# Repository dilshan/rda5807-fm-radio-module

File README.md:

# FM stereo receiver module

This is an RDA5807 based FM stereo radio module. This module is designed to replace old, low-voltage, analog FM stereo receiver modules. Like many digital receivers, this module also got auto scanning, station memory, and digital volume control. This module can driver using 5V to 9V DC power source.

The frequency range of the receiver is 88MHz to 108MHz. The auto scanner of this module can tune the receiver with 25kHz increments in up and down directions. 

The memory manager available with the current firmware can hold up to 10 stations in MCU EEPROM. 

AF output power of this module is not sufficient to handle the pair of speakers. To drive speakers, this module needs to pair with a stereo AF power amplifier kit/module.

This is a [certified open-source hardware project](https://certification.oshwa.org/lk000014.html). All the design files, [documentation](https://github.com/dilshan/rda5807-fm-radio-module/wiki), and firmware source code are available to download at the [project source repository](https://github.com/dilshan/rda5807-fm-radio-module/tree/main/firmware). Content of this project is distributed under the terms of the following license:

 - Hardware License: [CERN-OHL-W](https://opensource.org/CERN-OHL-W)
 - Software License: [MIT License](https://github.com/dilshan/rda5807-fm-radio-module/blob/main/LICENSE)
 - Documentation License: [CC BY 4.0](https://creativecommons.org/licenses/by/4.0)

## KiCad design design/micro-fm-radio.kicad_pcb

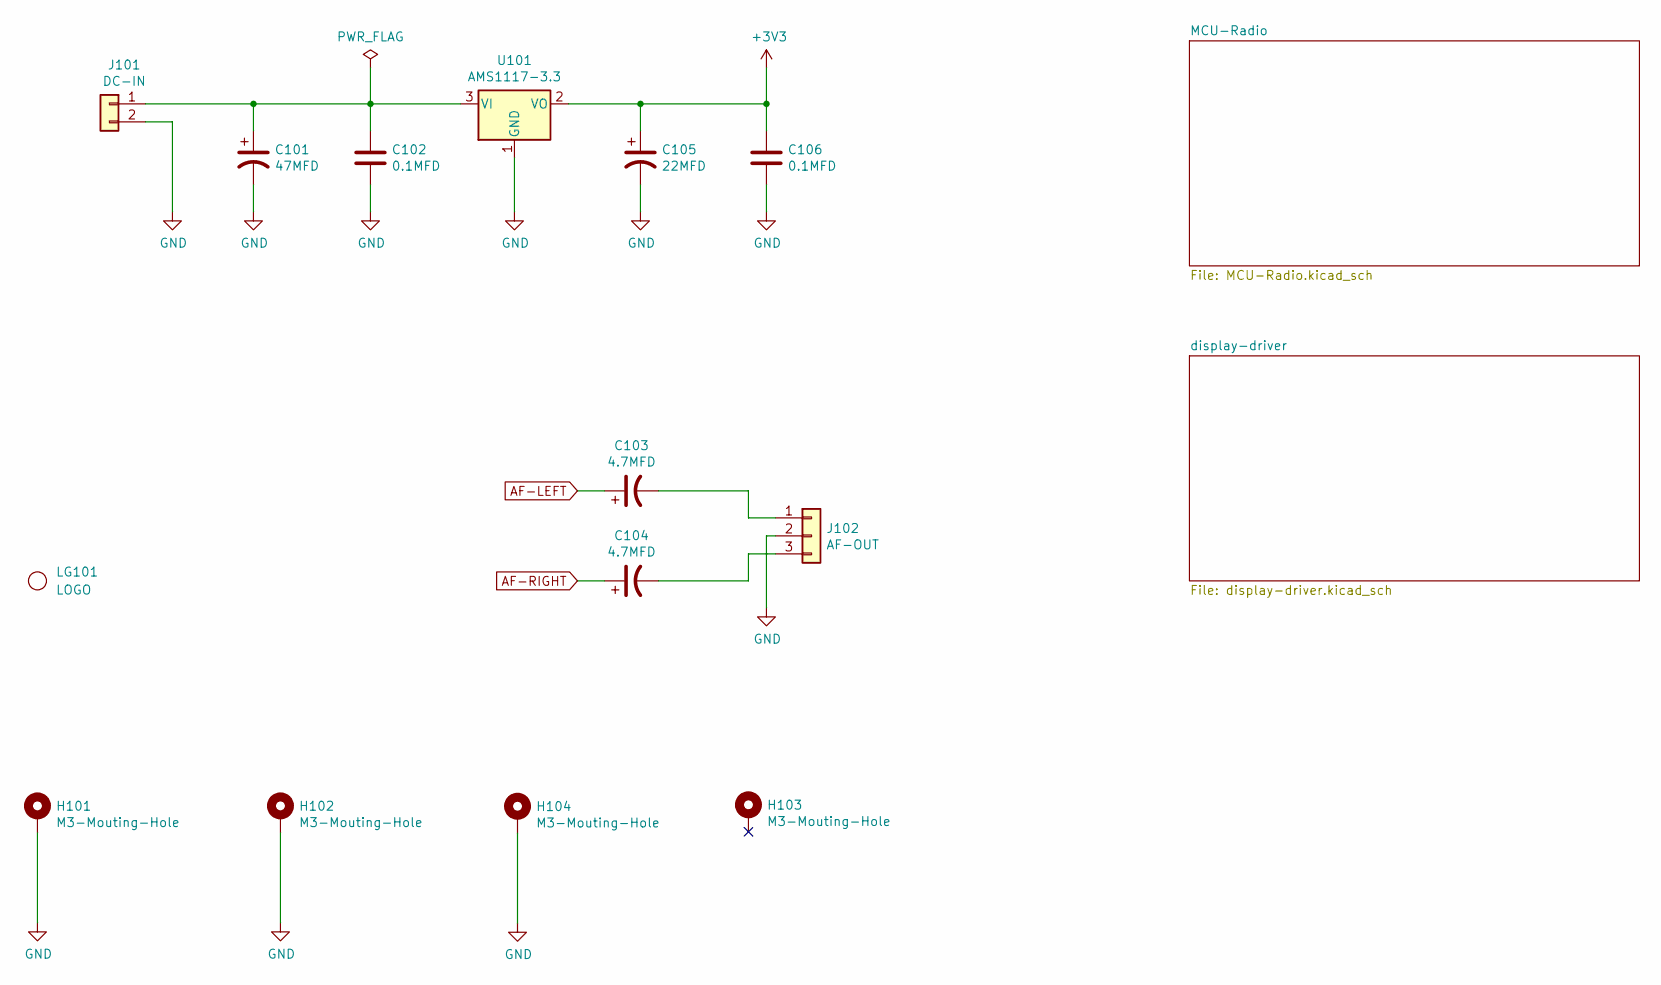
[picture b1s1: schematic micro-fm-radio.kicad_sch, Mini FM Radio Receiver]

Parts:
C101: 47MFD; CP_Radial_D5.0mm_P2.50mm
C102, C106: 0.1MFD; C_0805_2012Metric_Pad1.18x1.45mm_HandSolder
C103, C104: 4.7MFD; CP_Radial_D5.0mm_P2.50mm
C105: 22MFD; CP_Radial_D5.0mm_P2.50mm
H101, H102, H103, H104: M3-Mouting-Hole; MountingHole_3.2mm_M3_Pad
J101: DC-IN; PhoenixContact_MCV_1,5_2-G-3.5_1x02_P3.50mm_Vertical
J102: AF-OUT; PinHeader_1x03_P2.54mm_Vertical
LG101: LOGO; elect-6mm
U101: AMS1117-3.3; SOT-223-3_TabPin2

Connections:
+3V3: C105.1, C106.1, U101.2 (VO); also elsewhere on the board
AF-LEFT: C103.1; also elsewhere on the board
AF-RIGHT: C104.1; also elsewhere on the board
GND: C101.2, C102.2, C105.2, C106.2, H101.1, H102.1, H104.1, J101.2, J102.2, U101.1 (GND); also elsewhere on the board
unnamed: C101.1, C102.1, J101.1, U101.3 (VI)
unnamed: C103.2, J102.1
unnamed: C104.2, J102.3

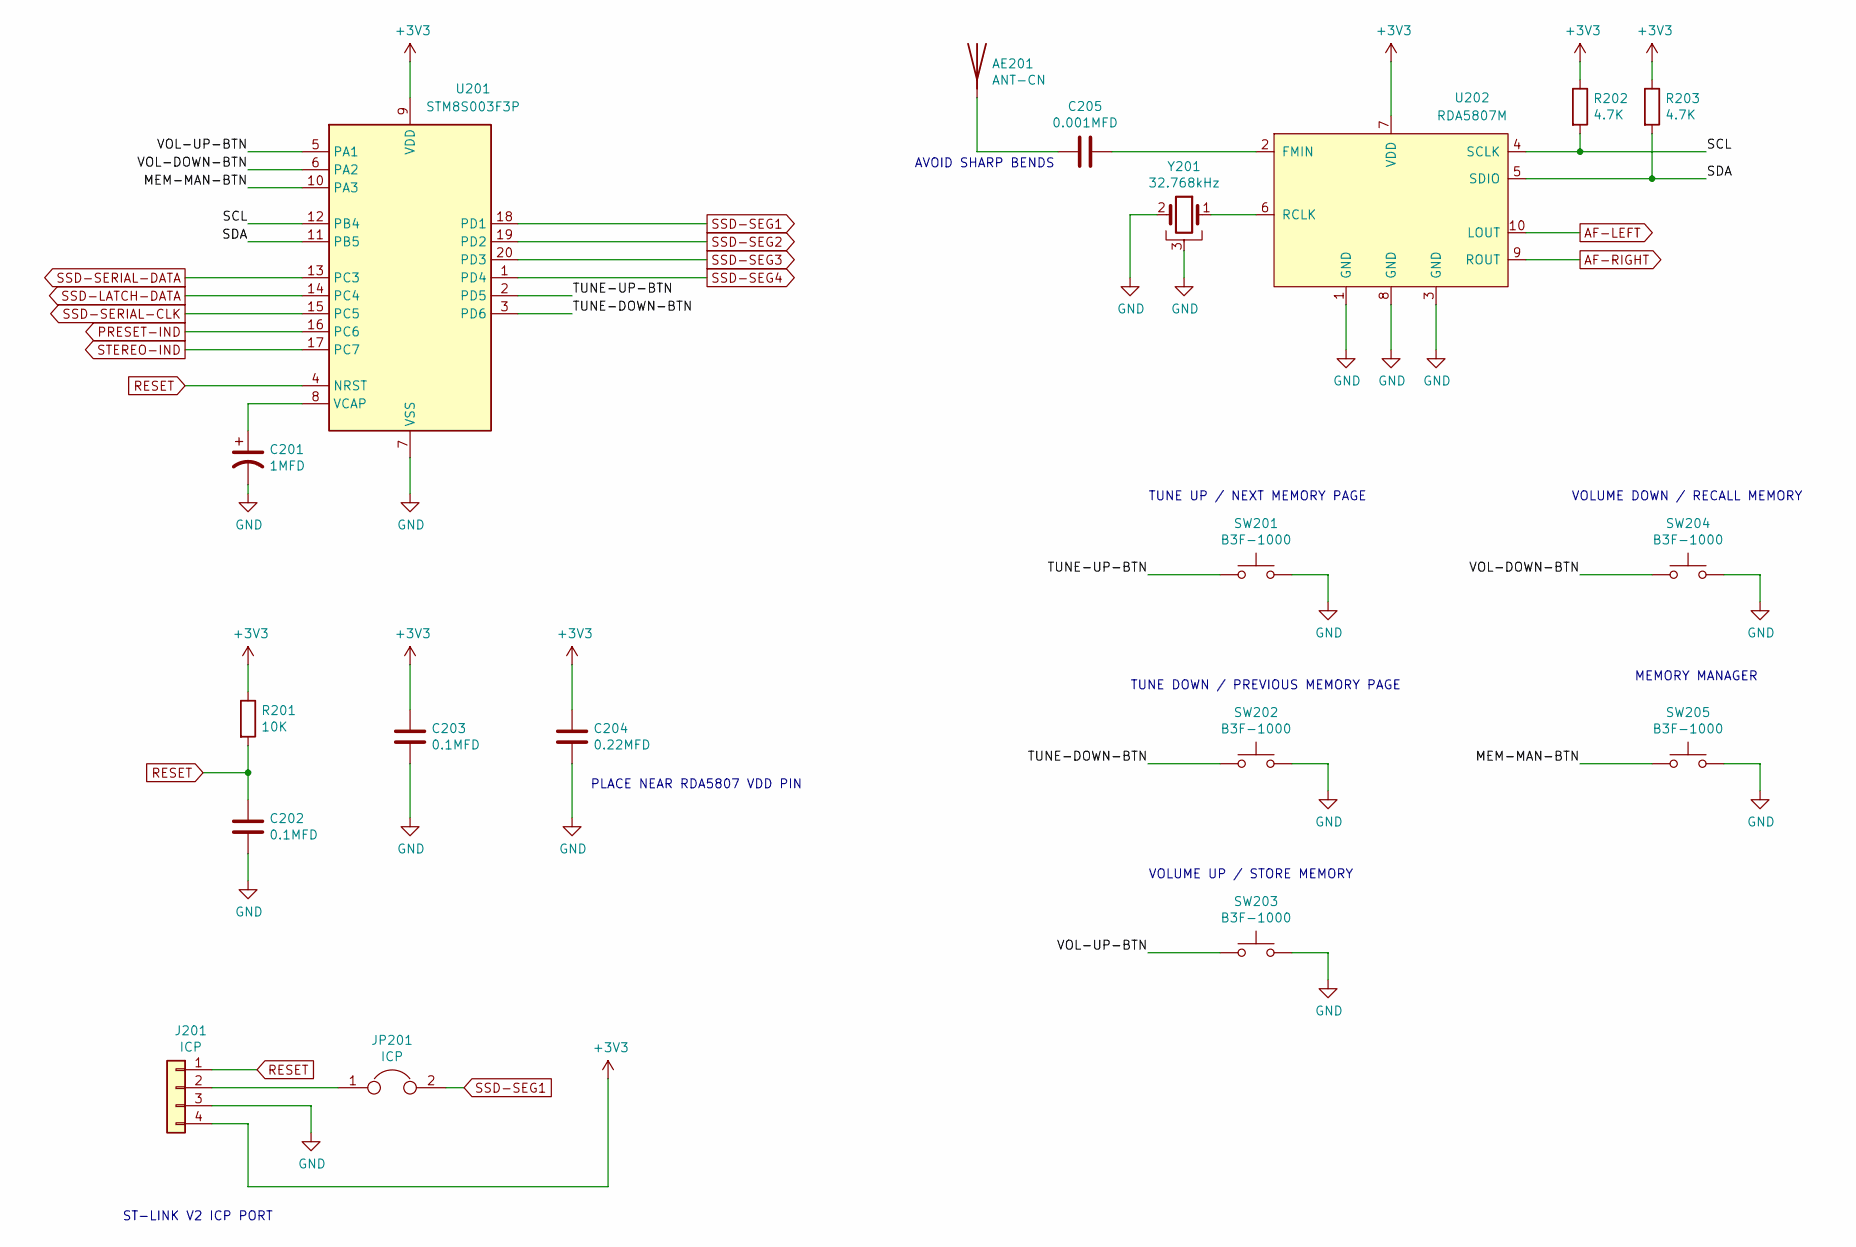
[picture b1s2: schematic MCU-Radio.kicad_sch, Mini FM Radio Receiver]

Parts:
AE201: ANT-CN; TestPoint_Loop_D2.50mm_Drill1.0mm
C201: 1MFD; C_0805_2012Metric_Pad1.18x1.45mm_HandSolder
C202, C203: 0.1MFD; C_0805_2012Metric_Pad1.18x1.45mm_HandSolder
C204: 0.22MFD; C_0805_2012Metric_Pad1.18x1.45mm_HandSolder
C205: 0.001MFD; C_0805_2012Metric_Pad1.18x1.45mm_HandSolder
J201: ICP; pogo-2.54mmx4
JP201: ICP; SolderJumper-2_P1.3mm_Bridged_Pad1.0x1.5mm
R201: 10K; R_0805_2012Metric_Pad1.20x1.40mm_HandSolder
R202, R203: 4.7K; R_0805_2012Metric_Pad1.20x1.40mm_HandSolder
SW201, SW202, SW203, SW204, SW205: B3F-1000; SW_PUSH_6mm
U201: STM8S003F3P; TSSOP-20_4.4x6.5mm_P0.65mm
U202: RDA5807M; MSOP-10_3x3mm_P0.5mm
Y201: 32.768kHz; Crystal_C38-LF_D3.0mm_L8.0mm_Horizontal_1EP_style2

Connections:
+3V3: C203.1, C204.1, J201.4, R201.1, R202.1, R203.1, U201.9 (VDD), U202.7 (VDD); also elsewhere on the board
/MCU-Radio/MEM-MAN-BTN: SW205.1, U201.10 (PA3)
/MCU-Radio/SCL: R202.2, U201.12 (PB4), U202.4 (SCLK)
/MCU-Radio/SDA: R203.2, U201.11 (PB5), U202.5 (SDIO)
/MCU-Radio/TUNE-DOWN-BTN: SW202.1, U201.3 (PD6)
/MCU-Radio/TUNE-UP-BTN: SW201.1, U201.2 (PD5)
/MCU-Radio/VOL-DOWN-BTN: SW204.1, U201.6 (PA2)
/MCU-Radio/VOL-UP-BTN: SW203.1, U201.5 (PA1)
AF-LEFT: U202.10 (LOUT); also elsewhere on the board
AF-RIGHT: U202.9 (ROUT); also elsewhere on the board
GND: C201.2, C202.2, C203.2, C204.2, J201.3, SW201.2, SW202.2, SW203.2, SW204.2, SW205.2, U201.7 (VSS), U202.1 (GND), U202.3 (GND), U202.8 (GND), Y201.2, Y201.3; also elsewhere on the board
unnamed: AE201.1 (A), C205.2
unnamed: C201.1, U201.8 (VCAP)
unnamed: C205.1, U202.2 (FMIN)
unnamed: J201.2, JP201.1
unnamed: U202.6 (RCLK), Y201.1
PRESET-IND: U201.16 (PC6); also elsewhere on the board
RESET: C202.1, J201.1, R201.2, U201.4 (NRST); also elsewhere on the board
SSD-LATCH-DATA: U201.14 (PC4); also elsewhere on the board
SSD-SEG1: JP201.2, U201.18 (PD1); also elsewhere on the board
SSD-SEG2: U201.19 (PD2); also elsewhere on the board
SSD-SEG3: U201.20 (PD3); also elsewhere on the board
SSD-SEG4: U201.1 (PD4); also elsewhere on the board
SSD-SERIAL-CLK: U201.15 (PC5); also elsewhere on the board
SSD-SERIAL-DATA: U201.13 (PC3); also elsewhere on the board
STEREO-IND: U201.17 (PC7); also elsewhere on the board

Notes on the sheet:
PLACE NEAR RDA5807 VDD PIN
MEMORY MANAGER
TUNE UP / NEXT MEMORY PAGE
ST-LINK V2 ICP PORT
AVOID SHARP BENDS
VOLUME UP / STORE MEMORY
TUNE DOWN / PREVIOUS MEMORY PAGE
VOLUME DOWN / RECALL MEMORY

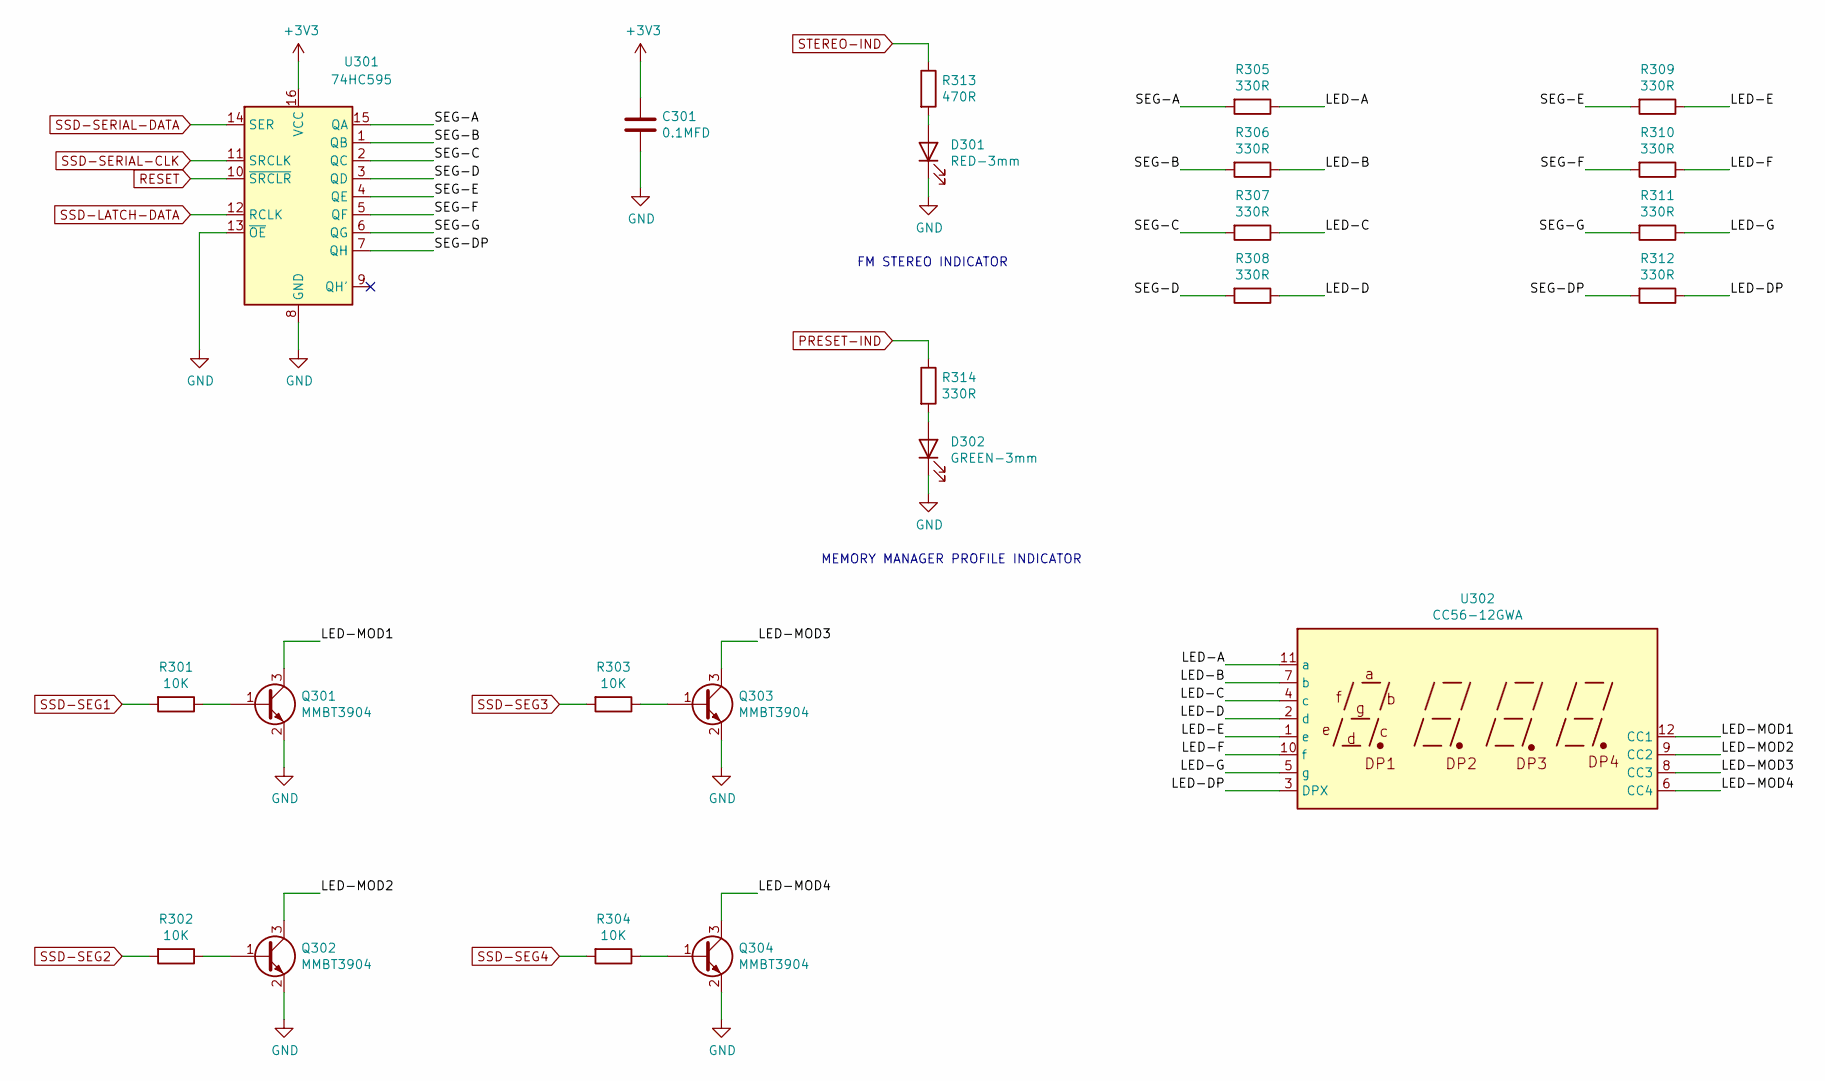
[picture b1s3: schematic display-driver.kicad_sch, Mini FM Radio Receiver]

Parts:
C301: 0.1MFD; C_0805_2012Metric_Pad1.18x1.45mm_HandSolder
D301: RED-3mm; LED_D3.0mm
D302: GREEN-3mm; LED_D3.0mm
Q301, Q302, Q303, Q304: MMBT3904; SOT-23
R301, R302, R303, R304: 10K; R_0805_2012Metric_Pad1.20x1.40mm_HandSolder
R305, R306, R307, R308, R309, R310, R311, R312, R314: 330R; R_0805_2012Metric_Pad1.20x1.40mm_HandSolder
R313: 470R; R_0805_2012Metric_Pad1.20x1.40mm_HandSolder
U301: 74HC595; SOP-16_4.4x10.4mm_P1.27mm
U302: CC56-12GWA

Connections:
+3V3: C301.1, U301.16 (VCC); also elsewhere on the board
/display-driver/LED-A: R305.1, U302.11 (a)
/display-driver/LED-B: R306.1, U302.7 (b)
/display-driver/LED-C: R307.1, U302.4 (c)
/display-driver/LED-D: R308.1, U302.2 (d)
/display-driver/LED-DP: R312.1, U302.3 (DPX)
/display-driver/LED-E: R309.1, U302.1 (e)
/display-driver/LED-F: R310.1, U302.10 (f)
/display-driver/LED-G: R311.1, U302.5 (g)
/display-driver/LED-MOD1: Q301.3 (C), U302.12 (CC1)
/display-driver/LED-MOD2: Q302.3 (C), U302.9 (CC2)
/display-driver/LED-MOD3: Q303.3 (C), U302.8 (CC3)
/display-driver/LED-MOD4: Q304.3 (C), U302.6 (CC4)
/display-driver/SEG-A: R305.2, U301.15 (QA)
/display-driver/SEG-B: R306.2, U301.1 (QB)
/display-driver/SEG-C: R307.2, U301.2 (QC)
/display-driver/SEG-D: R308.2, U301.3 (QD)
/display-driver/SEG-DP: R312.2, U301.7 (QH)
/display-driver/SEG-E: R309.2, U301.4 (QE)
/display-driver/SEG-F: R310.2, U301.5 (QF)
/display-driver/SEG-G: R311.2, U301.6 (QG)
GND: C301.2, D301.1 (K), D302.1 (K), Q301.2 (E), Q302.2 (E), Q303.2 (E), Q304.2 (E), U301.8 (GND), U301.13 (~OE); also elsewhere on the board
unnamed: D301.2 (A), R313.2
unnamed: D302.2 (A), R314.2
unnamed: Q301.1 (B), R301.1
unnamed: Q302.1 (B), R302.1
unnamed: Q303.1 (B), R303.1
unnamed: Q304.1 (B), R304.1
PRESET-IND: R314.1; also elsewhere on the board
RESET: U301.10 (~SRCLR); also elsewhere on the board
SSD-LATCH-DATA: U301.12 (RCLK); also elsewhere on the board
SSD-SEG1: R301.2; also elsewhere on the board
SSD-SEG2: R302.2; also elsewhere on the board
SSD-SEG3: R303.2; also elsewhere on the board
SSD-SEG4: R304.2; also elsewhere on the board
SSD-SERIAL-CLK: U301.11 (SRCLK); also elsewhere on the board
SSD-SERIAL-DATA: U301.14 (SER); also elsewhere on the board
STEREO-IND: R313.1; also elsewhere on the board

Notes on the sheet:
MEMORY MANAGER PROFILE INDICATOR
FM STEREO INDICATOR

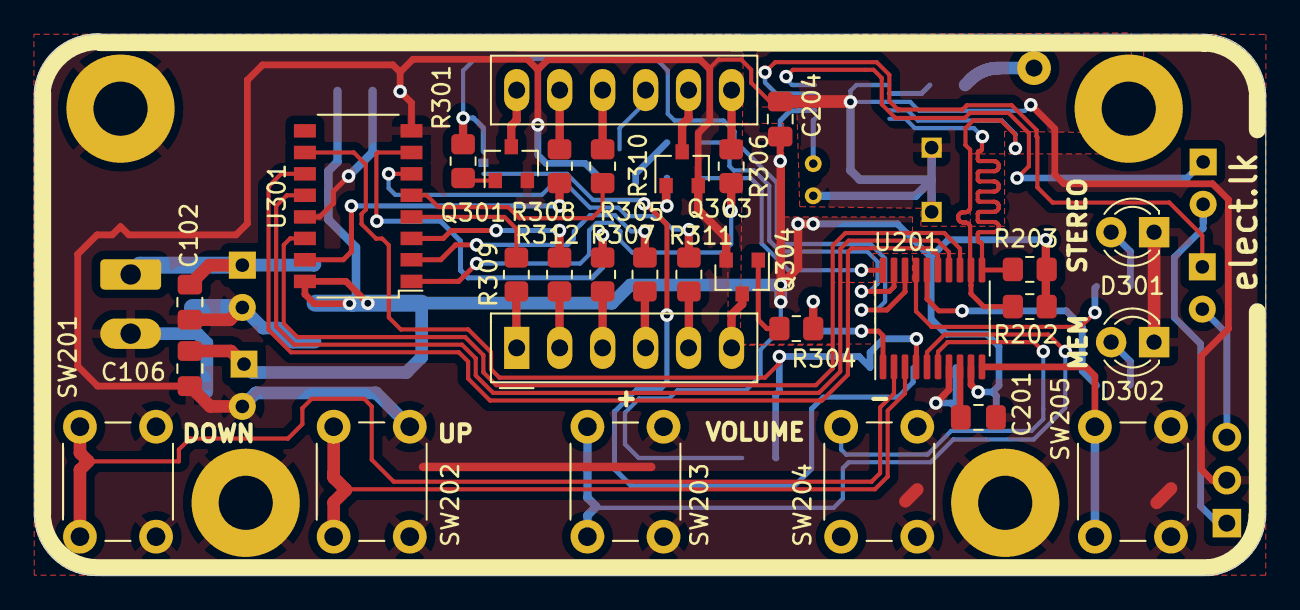
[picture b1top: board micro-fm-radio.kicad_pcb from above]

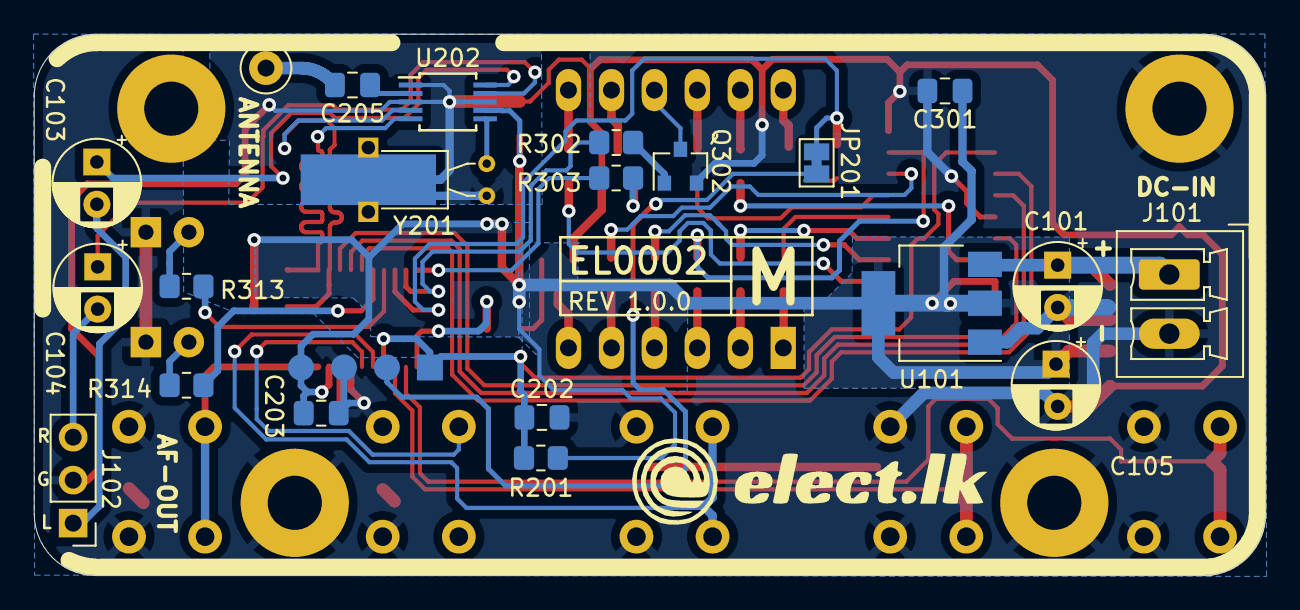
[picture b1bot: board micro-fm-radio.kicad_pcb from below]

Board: 2 copper layers, 72.8 x 32.0 mm, 56 parts (23 on the bottom side), 55 nets.

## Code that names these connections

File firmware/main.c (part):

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
void initSystem()
{
    // PC3 [OUT] : Serial data.
    // PC4 [OUT] : Latch data.
    // PC5 [OUT] : Serial clock.
    // PC6 [OUT] : Channel available in memory manager indicator (Preset channel).
    // PC7 [OUT] : Stereo indicator.
    PC_ODR = 0x00;
    PC_DDR = 0xF8;
    PC_CR1 = 0xF8;
    PC_CR2 = 0x00;  

    // PD1 [OUT] : Seven segment digit 1 driver.
    // PD2 [OUT] : Seven segment digit 2 driver.
    // PD3 [OUT] : Seven segment digit 3 driver.
    // PD4 [OUT] : Seven segment digit 4 driver. 
    // PD5 [IN]  : UP button.
    // PD6 [IN]  : DOWN button.
    PD_ODR = 0x00; 
    PD_DDR = 0x1E;
    PD_CR1 = 0x7E;
    PD_CR2 = 0x00;

    // PA1 [IN] : Volume UP button.
    // PA2 [IN] : Volume Down button.
    // PA3 [IN] : Memory.
    PA_DDR = 0x00;
    PA_CR1 = 0x0E;
    PA_CR2 = 0x00;
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
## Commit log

2025-03-22 Add initial version of schematic, PCB design and firmware files.
2025-03-22 Add initial version of readme file.
2025-03-22 Add LICENSE file.
2025-03-22 Add links to license file and firmware directory.
2025-03-22 Add module photographs, CAD drawings, and fritzing modules.
2025-03-22 Add module photograph to readme file.
2025-03-22 Add schematic in PDF format.
2025-03-22 Add link to documentation.
2025-03-28 Add OSHWA license image.
2025-03-28 Add OSHWA license information to the readme file.
